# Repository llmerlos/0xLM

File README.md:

# PICCTRL - 0xLM
## 3x6 + 3 Split Ortholinear Keyboard with on board MCU

## Why?
I wanted to make a compact keyboard by using the minimum surface for the keys with all the components underneath them while no increasing the height of the overall keyboard.

## Characteristics:
* CH559L [FAK](https://github.com/semickolon/fak) powered.
* Direct pin with ESD and over-current protection [[Schematic]](https://github.com/llmerlos/0xLM/blob/main/PCB/pdf/Board.pdf).
* [3D Printed Case](https://github.com/llmerlos/0xLM/tree/main/CASE).
* PCBA ready* (See Known Issues). 
* Choc V1 spacing.

## Pics

## Known Issues:
* USB part is a little bit missplaced and requires triming the legs (for a fee in JLCPCB).
* USB part is for 0.8mm PCB instead of 1.6mm PCB.
* BOOT silkscreen rotated 180 degrees on the right PCB.

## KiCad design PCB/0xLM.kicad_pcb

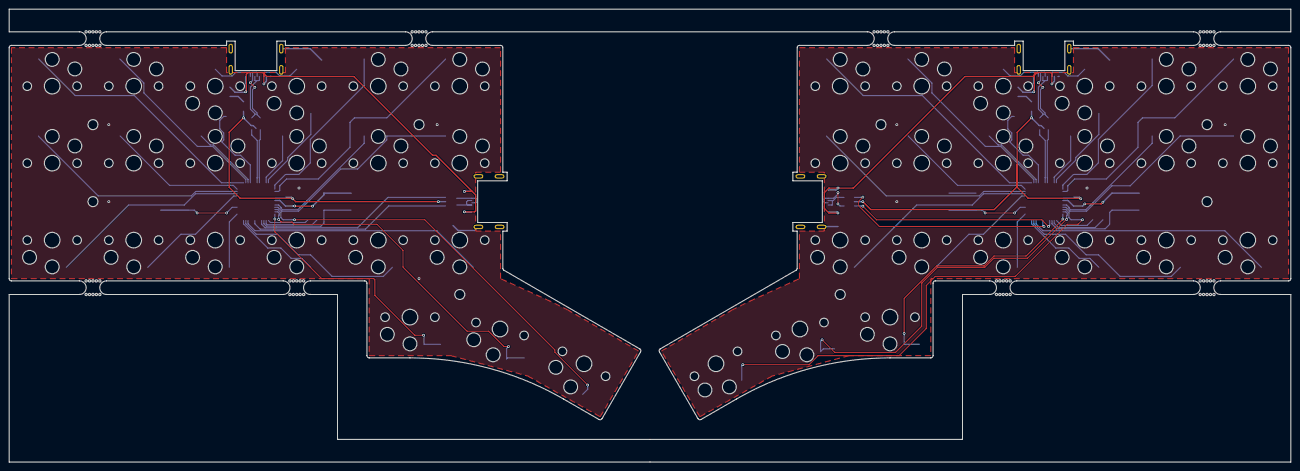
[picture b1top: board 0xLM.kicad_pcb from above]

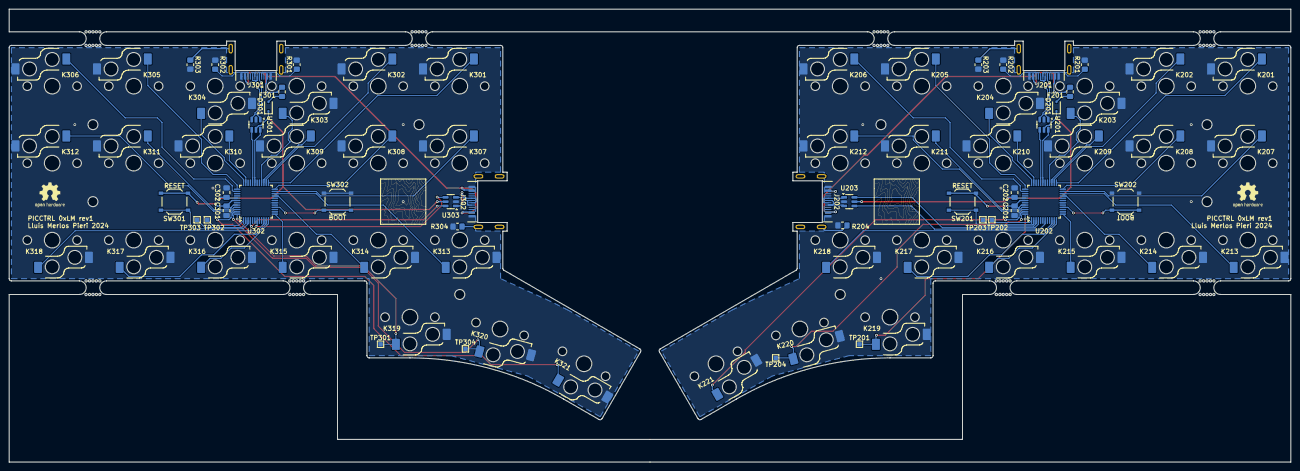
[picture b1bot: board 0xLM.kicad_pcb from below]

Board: 2 copper layers, 282.9 x 99.9 mm, 88 parts (80 on the bottom side), 81 nets.

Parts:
C201, C301: 3.3uF; C_0805_2012Metric_Pad1.18x1.45mm_HandSolder
C202, C302: 100nF; C_0805_2012Metric_Pad1.18x1.45mm_HandSolder
D201, D301: PMEG2010EA; D_SOD-323
F201, F301: 500mA; Fuse_0805_2012Metric_Pad1.15x1.40mm_HandSolder
J201, J202, J301, J302: TYPE-C-31-M-14
K201, K202, K203, K204, K205, K206, K207, K208, K209, K210, K211, K212, K213, K214, K215, K216, K217, K218, K219, K220, K221, K301, K302, K303, K304, K305, K306, K307, K308, K309, K310, K311, K312, K313, K314, K315, K316, K317, K318, K319, K320, K321: CPG135001S30; SW_Hotswap_Kailh_Choc_V1_1.00u
R201, R202, R301, R302: 5.1k; R_0805_2012Metric_Pad1.20x1.40mm_HandSolder
R203, R204, R303, R304: DNP; R_0805_2012Metric_Pad1.20x1.40mm_HandSolder
SW201, SW202, SW301, SW302: TS-1187A-B-A-B; SW_Push_1P1T_XKB_TS-1187A
TP201, TP301: TP_MOSI_1.5; TestPoint_Pad_1.0x1.0mm
TP202, TP302: TP_MISO_1.6; TestPoint_Pad_1.0x1.0mm
TP203, TP303: TP_SCK_1.7; TestPoint_Pad_1.0x1.0mm
TP204, TP304: TP_SCS_1.4; TestPoint_Pad_1.0x1.0mm
U201, U203, U301, U303: USBLC6-2SC6; SOT-23-6
U202, U302: CH559L; LQFP-48_7x7mm_P0.5mm
mouse-bite-3mm-slot, mouse-bite-3mm-slot#2, mouse-bite-3mm-slot#3, mouse-bite-3mm-slot#4, mouse-bite-3mm-slot#5, mouse-bite-3mm-slot#6, mouse-bite-3mm-slot#7, mouse-bite-3mm-slot#8: VAL**; mouse-bite-3mm-slot

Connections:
+3V3: C201.1, C301.1, SW201.2, SW301.2, U202.42 (VDD33), U302.42 (VDD33)
+5V: C202.1, C302.1, D201.1 (K), D301.1 (K), U201.5 (VBUS), U202.41 (VIN5), U203.5 (VBUS), U301.5 (VBUS), U302.41 (VIN5), U303.5 (VBUS)
/BoardL/BOOT: SW202.2, U202.16 (P4.6/XI/SCS_)
/BoardL/D+: U201.6 (I/O1), U202.31 (P5.1/DP)
/BoardL/D-: U201.4 (I/O2), U202.32 (P5.0/DM)
/BoardL/K1: K201.1, U202.25 (P2.4/PWM1/A12)
/BoardL/K2: K202.1, U202.26 (P2.5/TNOW/PWM2/A13/T2EX_/CAP2_)
/BoardL/K3: K203.1, U202.28 (P2.7/TXD1/DA7/A15)
/BoardL/K4: K204.1, U202.36 (P0.4/AD4/UCTS)
/BoardL/K5: K205.1, U202.37 (P0.3/AD3/TXD_)
/BoardL/K6: K206.1, U202.38 (P0.2/AD2/RXD_)
/BoardL/K7: K207.1, U202.23 (P2.2/MISO1/A10)
/BoardL/K8: K208.1, U202.24 (P2.3/SCK1/A11)
/BoardL/K9: K209.1, U202.27 (P2.6/RXD1/A14)
/BoardL/K10: K210.1, U202.35 (P0.5/AD5/UDSR)
/BoardL/K11: K211.1, U202.44 (P1.1/AIN1/T2EX/CAP2)
/BoardL/K12: K212.1, U202.45 (P1.2/AIN2/PWM3/CAP3)
/BoardL/K13: K213.1, U202.22 (P2.1/MOSI1/A9)
/BoardL/K14: K214.1, U202.21 (P2.0/A8)
/BoardL/K15: K215.1, U202.13 (P3.7/RD)
/BoardL/K16: K216.1, U202.12 (P3.6/WR)
/BoardL/K17: K217.1, U202.11 (P3.5/DA6/T1)
/BoardL/K18: K218.1, U202.10 (P3.4/LEDC/XCS0/T0)
/BoardL/K19: K219.1, TP201.1, U202.48 (P1.5/AIN5/MOSI)
/BoardL/K20: K220.1, TP204.1, U202.47 (P1.4/AIN4/SCS)
/BoardL/K21: K221.1, U202.46 (P1.3/AIN3)
/BoardL/P_D+: J201.A6 (D+), J201.B6 (D+), U201.1 (I/O1)
/BoardL/P_D-: J201.A7 (D-), J201.B7 (D-), U201.3 (I/O2)
/BoardL/P_RX: J202.A7 (D-), J202.B7 (D-), U203.1 (I/O1)
/BoardL/P_TX: J202.A6 (D+), J202.B6 (D+), U203.3 (I/O2)
/BoardL/RST: SW201.1, U202.3 (P5.7/RST)
/BoardL/RX: U202.4 (P3.0/RXD), U203.6 (I/O1)
/BoardL/TX: U202.7 (P3.1/TXD), U203.4 (I/O2)
/BoardL/VBUS: F201.2, J201.A4 (VBUS), J201.A9 (VBUS), J201.B4 (VBUS), J201.B9 (VBUS), J202.A4 (VBUS), J202.A9 (VBUS), J202.B4 (VBUS), J202.B9 (VBUS)
/BoardR/BOOT: SW302.2, U302.16 (P4.6/XI/SCS_)
/BoardR/D+: U301.6 (I/O1), U302.31 (P5.1/DP)
/BoardR/D-: U301.4 (I/O2), U302.32 (P5.0/DM)
/BoardR/K1: K301.1, U302.25 (P2.4/PWM1/A12)
/BoardR/K2: K302.1, U302.26 (P2.5/TNOW/PWM2/A13/T2EX_/CAP2_)
/BoardR/K3: K303.1, U302.28 (P2.7/TXD1/DA7/A15)
/BoardR/K4: K304.1, U302.36 (P0.4/AD4/UCTS)
/BoardR/K5: K305.1, U302.37 (P0.3/AD3/TXD_)
/BoardR/K6: K306.1, U302.38 (P0.2/AD2/RXD_)
/BoardR/K7: K307.1, U302.23 (P2.2/MISO1/A10)
/BoardR/K8: K308.1, U302.24 (P2.3/SCK1/A11)
/BoardR/K9: K309.1, U302.27 (P2.6/RXD1/A14)
/BoardR/K10: K310.1, U302.35 (P0.5/AD5/UDSR)
/BoardR/K11: K311.1, U302.44 (P1.1/AIN1/T2EX/CAP2)
/BoardR/K12: K312.1, U302.45 (P1.2/AIN2/PWM3/CAP3)
/BoardR/K13: K313.1, U302.22 (P2.1/MOSI1/A9)
/BoardR/K14: K314.1, U302.21 (P2.0/A8)
/BoardR/K15: K315.1, U302.13 (P3.7/RD)
/BoardR/K16: K316.1, U302.12 (P3.6/WR)
/BoardR/K17: K317.1, U302.11 (P3.5/DA6/T1)
/BoardR/K18: K318.1, U302.10 (P3.4/LEDC/XCS0/T0)
/BoardR/K19: K319.1, TP301.1, U302.48 (P1.5/AIN5/MOSI)
/BoardR/K20: K320.1, TP304.1, U302.47 (P1.4/AIN4/SCS)
/BoardR/K21: K321.1, U302.46 (P1.3/AIN3)
/BoardR/P_D+: J301.A6 (D+), J301.B6 (D+), U301.1 (I/O1)
/BoardR/P_D-: J301.A7 (D-), J301.B7 (D-), U301.3 (I/O2)
/BoardR/P_RX: J302.A7 (D-), J302.B7 (D-), U303.1 (I/O1)
/BoardR/P_TX: J302.A6 (D+), J302.B6 (D+), U303.3 (I/O2)
/BoardR/RST: SW301.1, U302.3 (P5.7/RST)
/BoardR/RX: U302.4 (P3.0/RXD), U303.6 (I/O1)
/BoardR/TX: U302.7 (P3.1/TXD), U303.4 (I/O2)
/BoardR/VBUS: F301.2, J301.A4 (VBUS), J301.A9 (VBUS), J301.B4 (VBUS), J301.B9 (VBUS), J302.A4 (VBUS), J302.A9 (VBUS), J302.B4 (VBUS), J302.B9 (VBUS)
GND: C201.2, C202.2, C301.2, C302.2, J201.A1 (GND), J201.A12 (GND), J201.B1 (GND), J201.B12 (GND), J202.A1 (GND), J202.A12 (GND), J202.B1 (GND), J202.B12 (GND), J301.A1 (GND), J301.A12 (GND), J301.B1 (GND), J301.B12 (GND), J302.A1 (GND), J302.A12 (GND), J302.B1 (GND), J302.B12 (GND), K201.2, K202.2, K203.2, K204.2, K205.2, K206.2, K207.2, K208.2, K209.2, K210.2, K211.2, K212.2, K213.2, K214.2, K215.2, K216.2, K217.2, K218.2, K219.2, K220.2, K221.2, K301.2, K302.2, K303.2, K304.2, K305.2, K306.2, K307.2, K308.2, K309.2, K310.2, K311.2, K312.2, K313.2, K314.2, K315.2, K316.2, K317.2, K318.2, K319.2, K320.2, K321.2, R201.2, R202.1, R203.2, R204.2, R301.2, R302.1, R303.2, R304.2, SW202.1, SW302.1, U201.2 (GND), U202.18 (GND/VSS), U203.2 (GND), U301.2 (GND), U302.18 (GND/VSS), U303.2 (GND)
unnamed: D201.2 (A), F201.1
unnamed: D301.2 (A), F301.1
unnamed: J201.A5 (CC1), R201.1
unnamed: J201.B5 (CC2), R202.2
unnamed: J201.S1 (SHIELD), R203.1
unnamed: J202.S1 (SHIELD), R204.1
unnamed: J301.A5 (CC1), R301.1
unnamed: J301.B5 (CC2), R302.2
unnamed: J301.S1 (SHIELD), R303.1
unnamed: J302.S1 (SHIELD), R304.1
unnamed: TP202.1, U202.1 (P1.6/AIN6/MISO)
unnamed: TP203.1, U202.2 (P1.7/AIN7/SCK)
unnamed: TP302.1, U302.1 (P1.6/AIN6/MISO)
unnamed: TP303.1, U302.2 (P1.7/AIN7/SCK)

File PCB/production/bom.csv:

Designator,Footprint,Quantity,Value,LCSC Part #
"_8, _7, _6, _5, _4, _3, _2, ",,8,,
"C201, C301",0805,2,3.3uF,
"C202, C302",0805,2,100nF,
"D201, D301",D_SOD-323,2,PMEG2010EA,C193668
"F201, F301",0805,2,500mA,C311055
"J201, J202, J301, J302",TYPE-C-31-M-14,4,TYPE-C-31-M-14,C223907
"K201, K202, K203, K204, K205, K206, K207, K208, K209, K210, K211, K212, K213, K214, K215, K216, K217, K218, K219, K220, K221, K301, K302, K303, K304, K305, K306, K307, K308, K309, K310, K311, K312, K313, K314, K315, K316, K317, K318, K319, K320, K321",SW_Hotswap_Kailh_Choc_V1_1.00u,42,CPG135001S30,C5333465
"R201, R202, R301, R302",0805,4,5.1k,
"SW201, SW202, SW301, SW302",SW_Push_1P1T_XKB_TS-1187A,4,TS-1187A-B-A-B,
"U201, U203, U301, U303",SOT-23-6,4,USBLC6-2SC6,
"U202, U302",LQFP-48_7x7mm_P0.5mm,2,CH559L,
"mouse-bite-3mm-slot_8, mouse-bite-3mm-slot_7, mouse-bite-3mm-slot_6, mouse-bite-3mm-slot_5, mouse-bite-3mm-slot_4, mouse-bite-3mm-slot_3, mouse-bite-3mm-slot_2, mouse-bite-3mm-slot",mouse-bite-3mm-slot,8,VAL**,

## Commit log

2024-04-23 fixed links
2024-04-23 added stl
